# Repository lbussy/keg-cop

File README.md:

# Keg Cop

*Beverage Lines, Monitored.*

Keg Cop is an inexpensive and, most of all, simple to operate WiFi-enabled solution to maintain information about your Keezer, Kegerator, and Kegs.  Keg Cop enables you to use flowmeters of your choice (Swissflow during development) to monitor the contents of your kegs, and it even has a built-in Web UI to display what is on tap and how much is left.

Keg Cop uses an inexpensive ESP32 controller to control and monitor all aspects of your beverage dispensing solution.  If you already have flowmeters from another project, you can easily use those and upgrade your approach.  It will support one to nine flowmeters, and it will even control your temperatures for you.

You may employ up to five different temperature sensors to show you things like tower temp, keg temp, top and bottom of your Keezer, and you can even monitor the room temperature.

I designed this project as a complete system from the ground up.  Everything is provided, including board files for PCBs and 3D models for cases.  I’m releasing this system as something which provides either a complete recipe for success or enough information to allow you to roll your own if that’s your thing.

Whether you have one flowmeter or nine, Keg Cop can handle them.  Have more?  Add another controller, and KegScreen (coming soon!) will seamlessly display them all.

Want even more capabilities?  Keg Cop will report pours to Raspberry Pints via MQTT or a web endpoint with a generic JSON packet.
Still not enough?  Keg Cop was designed alongside KegScreen to work hand in hand with this exciting upcoming full-featured tap list solution.

Full documentation is provided, including the API and hardware assembly.  Or, if you are a more nuts and bolts person, GitHub may be the place for you!

Links and Support:

-	Home Page
-	Project on GitHub
-	Documentation
-	Report an Issue or Bug
-	Get support or chat with other users

This release has been a long time coming, and I’m excited to share this with you.  I want to thank the following folks from Homebrewtalk who have contributed in one way or another:

-	@thorrak
-	@gromitdj
-	@UncleD
-	@day_trippr
-	@cripplecreek

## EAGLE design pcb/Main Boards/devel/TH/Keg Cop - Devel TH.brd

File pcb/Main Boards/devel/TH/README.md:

# Development Board

It is exceedingly unlikely that anyone but me will need this PCB.

I designed this to allow me a physical interface into the software for development work.  This provides pushbuttons for emulating flowmeters, and a few DS18B20's for temperature values.

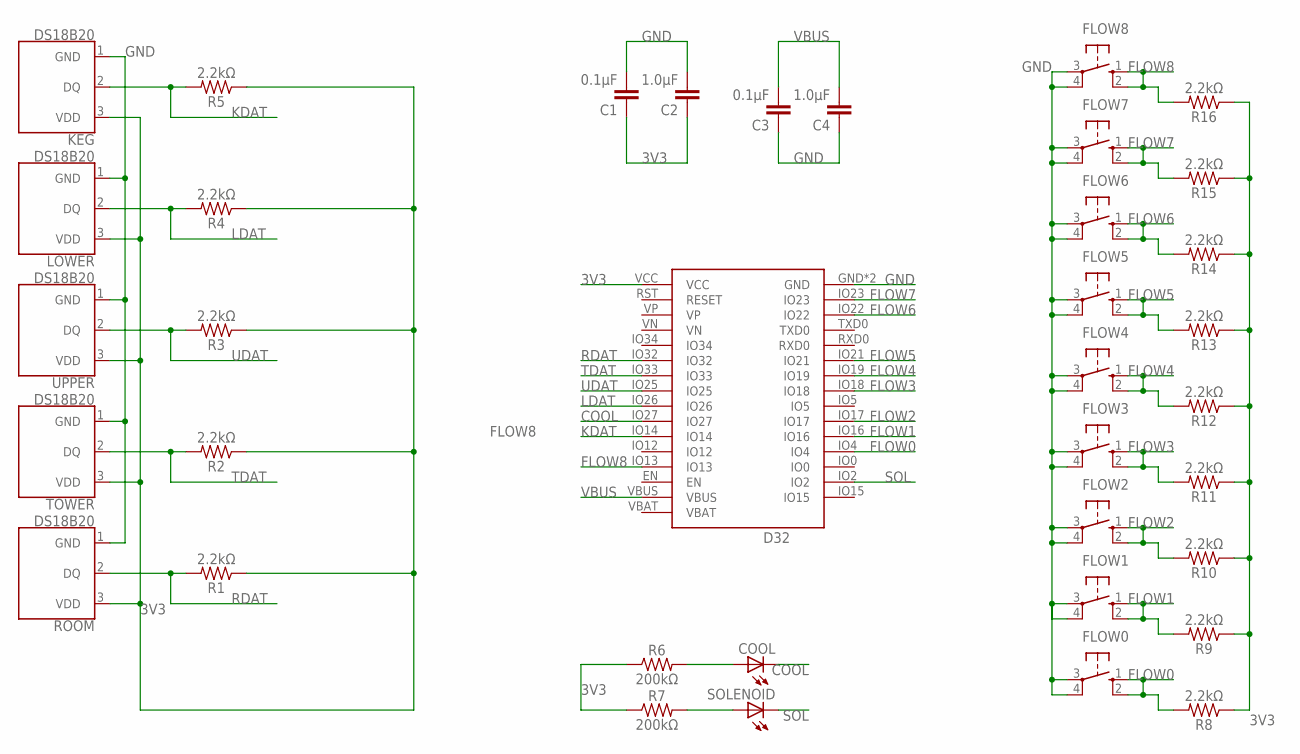
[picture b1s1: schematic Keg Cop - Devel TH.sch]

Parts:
C1, C3: 0.1μF; CAP_PTH-2.54
C2, C4: 1.0μF; CAP_PTH-2.54
COOL: LED3MM
D32: Lolin D32; D32_NO_BATT
FLOW0, FLOW1, FLOW2, FLOW3, FLOW4, FLOW5, FLOW6, FLOW7, FLOW8: 10-XX; B3F-10XX
KEG: DS18B20; TO-92-AMMO
LOWER: DS18B20; TO-92-AMMO
R1, R2, R3, R4, R5, R8, R9, R10, R11, R12, R13, R14, R15, R16: 2.2kΩ; AXIAL-0.3
R6, R7: 200kΩ; AXIAL-0.3
ROOM: DS18B20; TO-92-AMMO
SOLENOID: LED3MM
TOWER: DS18B20; TO-92-AMMO
UPPER: DS18B20; TO-92-AMMO

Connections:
3V3: C1.1, C2.1, D32.VCC, KEG.3 (VDD), LOWER.3 (VDD), R1.P$1 (1), R2.P$1 (1), R3.P$1 (1), R4.P$1 (1), R5.P$1 (1), R6.P$1 (1), R7.P$1 (1), R8.P$1 (1), R9.P$1 (1), R10.P$1 (1), R11.P$1 (1), R12.P$1 (1), R13.P$1 (1), R14.P$1 (1), R15.P$1 (1), R16.P$1 (1), ROOM.3 (VDD), TOWER.3 (VDD), UPPER.3 (VDD)
COOL: COOL.K (C), D32.IO27
FLOW0: D32.IO4, FLOW0.1 (S), FLOW0.2 (S1), R8.P$2 (2)
FLOW1: D32.IO16, FLOW1.1 (S), FLOW1.2 (S1), R9.P$2 (2)
FLOW2: D32.IO17, FLOW2.1 (S), FLOW2.2 (S1), R10.P$2 (2)
FLOW3: D32.IO18, FLOW3.1 (S), FLOW3.2 (S1), R11.P$2 (2)
FLOW4: D32.IO19, FLOW4.1 (S), FLOW4.2 (S1), R12.P$2 (2)
FLOW5: D32.IO21, FLOW5.1 (S), FLOW5.2 (S1), R13.P$2 (2)
FLOW6: D32.IO22, FLOW6.1 (S), FLOW6.2 (S1), R14.P$2 (2)
FLOW7: D32.IO23, FLOW7.1 (S), FLOW7.2 (S1), R15.P$2 (2)
FLOW8: D32.IO13, FLOW8.1 (S), FLOW8.2 (S1), R16.P$2 (2)
GND: C1.2, C2.2, C3.1, C4.1, D32.GND, D32.GND2 (GND), FLOW0.3, FLOW0.4 (P1), FLOW1.3, FLOW1.4 (P1), FLOW2.3, FLOW2.4 (P1), FLOW3.3, FLOW3.4 (P1), FLOW4.3, FLOW4.4 (P1), FLOW5.3, FLOW5.4 (P1), FLOW6.3, FLOW6.4 (P1), FLOW7.3, FLOW7.4 (P1), FLOW8.3, FLOW8.4 (P1), KEG.1 (GND), LOWER.1 (GND), ROOM.1 (GND), TOWER.1 (GND), UPPER.1 (GND)
KDAT: D32.IO14, KEG.2 (DQ), R5.P$2 (2)
LDAT: D32.IO26, LOWER.2 (DQ), R4.P$2 (2)
unnamed: COOL.A, R6.P$2 (2)
unnamed: R7.P$2 (2), SOLENOID.A
RDAT: D32.IO32, R1.P$2 (2), ROOM.2 (DQ)
SOL: D32.IO2, SOLENOID.K (C)
TDAT: D32.IO33, R2.P$2 (2), TOWER.2 (DQ)
UDAT: D32.IO25, R3.P$2 (2), UPPER.2 (DQ)
VBUS: C3.2, C4.2, D32.VBUS

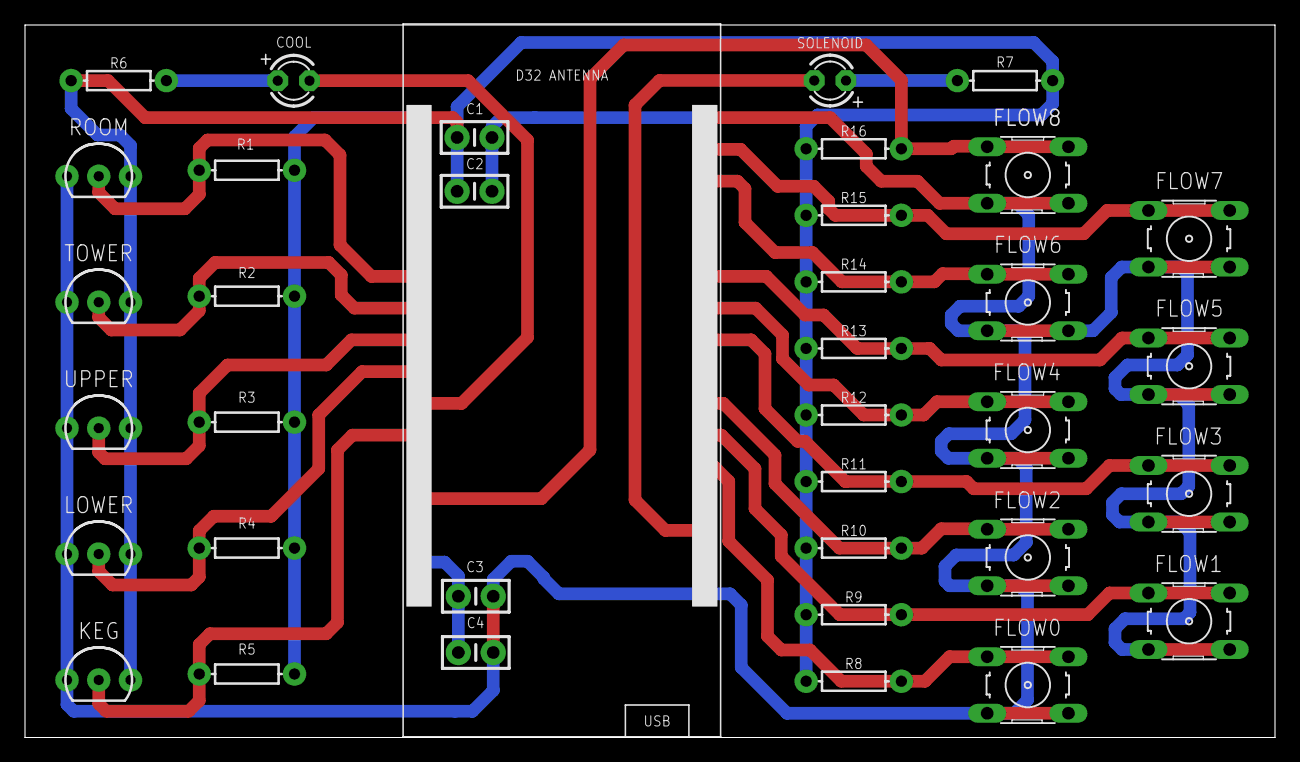
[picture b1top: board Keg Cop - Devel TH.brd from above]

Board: 2 copper layers, 100.0 x 57.0 mm, 37 parts (0 on the bottom side), 21 nets.

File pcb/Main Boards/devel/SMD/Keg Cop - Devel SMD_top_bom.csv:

Comment,Designator,Footprint,LCSC Part #
0.1µF,C1 C3,SMD-0805,C28233
1.0µF,C2 C4,SMD-0805,C28323
2k2½,R1 R2 R3 R4 R5 R6 R7 R8 R9 R12 R13 R14 R15 R16,SMD-0805,C17518
60.4½,R10 R11,SMD-0805,C25323
DS18B20Z,KEG LOWER ROOM TOWER UPPER,SOIC127P600X175-8N,C695837
LED_0603LED_SMD_0603,COOL SOLENOID,LED_SMD_0603,C2286
TS08-66-43-BK-160-SMT-67,FLOW0 FLOW1 FLOW2 FLOW3 FLOW4 FLOW5 FLOW6 FLOW7 FLOW8,SW_TS08-66-43-BK-160-SMT-67,C2889023

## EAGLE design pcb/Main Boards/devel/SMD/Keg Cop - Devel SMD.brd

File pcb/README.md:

# Printed Circuit Boards for Keg Cop

Contained here are two folders:

- **Main Boards:** Boards which receive the D32 controller, and provide connectivity to the breakouts.
- **Breakouts:** Boards which distribute and receive signals within the kegerator/keezer.

The type and number required of each board will vary by the intended configuration.  Use [the documentation](https://docs.kegcop.com) to determine which boards you need and how many:

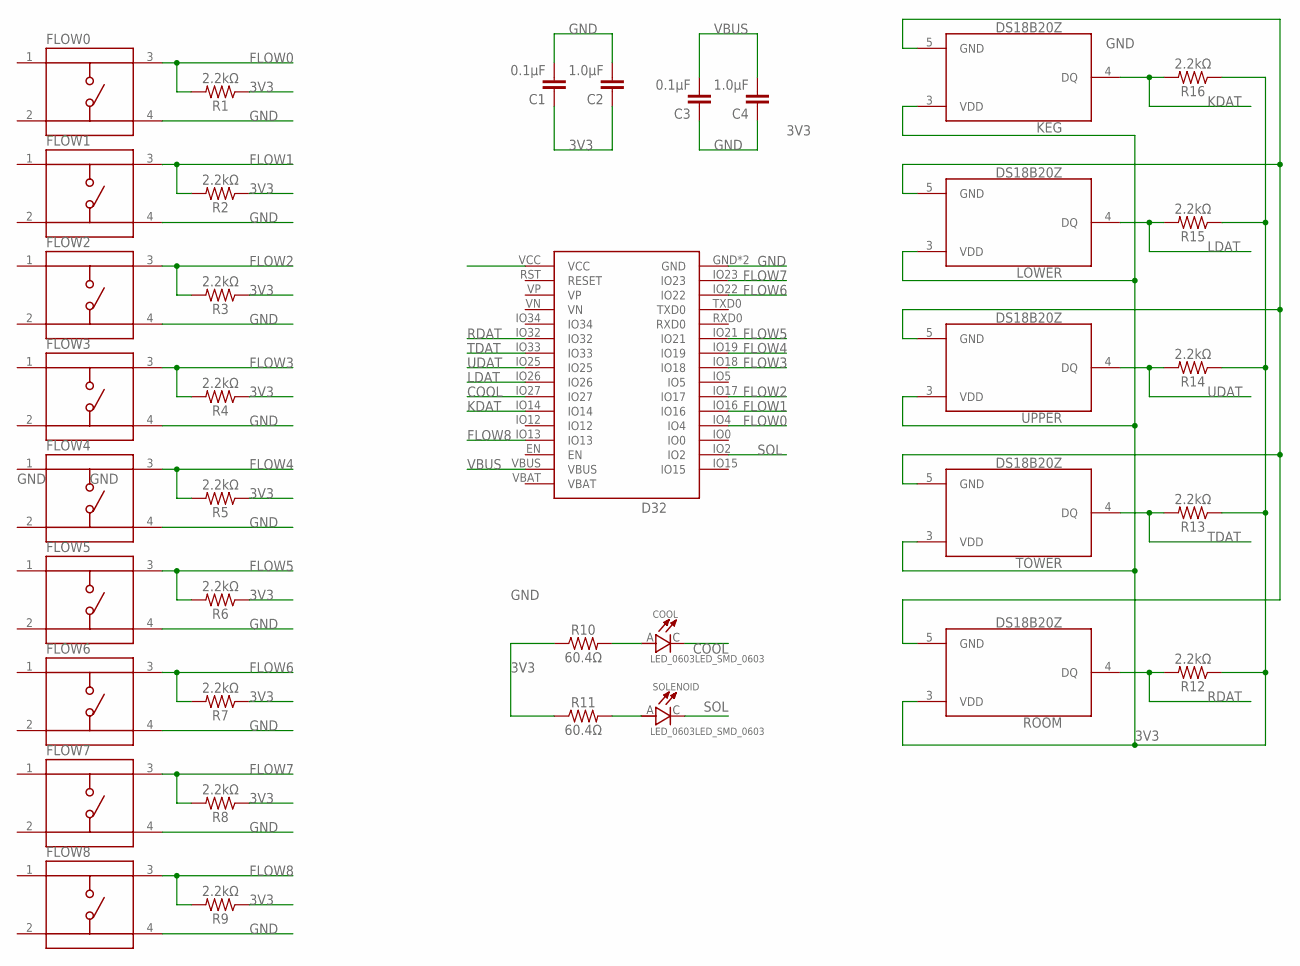
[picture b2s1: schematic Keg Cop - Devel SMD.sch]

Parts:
C1, C3: 0.1μF; SMD-0805
C2, C4: 1.0μF; SMD-0805
COOL: LED_0603LED_SMD_0603; LED_SMD_0603
D32: Lolin D32; D32_NO_BATT
FLOW0, FLOW1, FLOW2, FLOW3, FLOW4, FLOW5, FLOW6, FLOW7, FLOW8: TS08-66-43-BK-160-SMT-67; SW_TS08-66-43-BK-160-SMT-67
KEG: DS18B20Z; SOIC127P600X175-8N
LOWER: DS18B20Z; SOIC127P600X175-8N
R1, R2, R3, R4, R5, R6, R7, R8, R9, R12, R13, R14, R15, R16: 2.2kΩ; SMD-0805
R10, R11: 60.4Ω; SMD-0805
ROOM: DS18B20Z; SOIC127P600X175-8N
SOLENOID: LED_0603LED_SMD_0603; LED_SMD_0603
TOWER: DS18B20Z; SOIC127P600X175-8N
UPPER: DS18B20Z; SOIC127P600X175-8N

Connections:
3V3: C1.1, C2.1, D32.VCC, KEG.3 (VDD), LOWER.3 (VDD), R1.1, R2.1, R3.1, R4.1, R5.1, R6.1, R7.1, R8.1, R9.1, R10.1, R11.1, R12.1, R13.1, R14.1, R15.1, R16.1, ROOM.3 (VDD), TOWER.3 (VDD), UPPER.3 (VDD)
COOL: COOL.C, D32.IO27
FLOW0: D32.IO4, FLOW0.3, R1.2
FLOW1: D32.IO16, FLOW1.3, R2.2
FLOW2: D32.IO17, FLOW2.3, R3.2
FLOW3: D32.IO18, FLOW3.3, R4.2
FLOW4: D32.IO19, FLOW4.3, R5.2
FLOW5: D32.IO21, FLOW5.3, R6.2
FLOW6: D32.IO22, FLOW6.3, R7.2
FLOW7: D32.IO23, FLOW7.3, R8.2
FLOW8: D32.IO13, FLOW8.3, R9.2
GND: C1.2, C2.2, C3.1, C4.1, D32.GND, D32.GND2 (GND), FLOW0.4, FLOW1.4, FLOW2.4, FLOW3.4, FLOW4.4, FLOW5.4, FLOW6.4, FLOW7.4, FLOW8.4, KEG.5 (GND), LOWER.5 (GND), ROOM.5 (GND), TOWER.5 (GND), UPPER.5 (GND)
KDAT: D32.IO14, KEG.4 (DQ), R16.2
LDAT: D32.IO26, LOWER.4 (DQ), R15.2
unnamed: COOL.A, R10.2
unnamed: R11.2, SOLENOID.A
RDAT: D32.IO32, R12.2, ROOM.4 (DQ)
SOL: D32.IO2, SOLENOID.C
TDAT: D32.IO33, R13.2, TOWER.4 (DQ)
UDAT: D32.IO25, R14.2, UPPER.4 (DQ)
VBUS: C3.2, C4.2, D32.VBUS

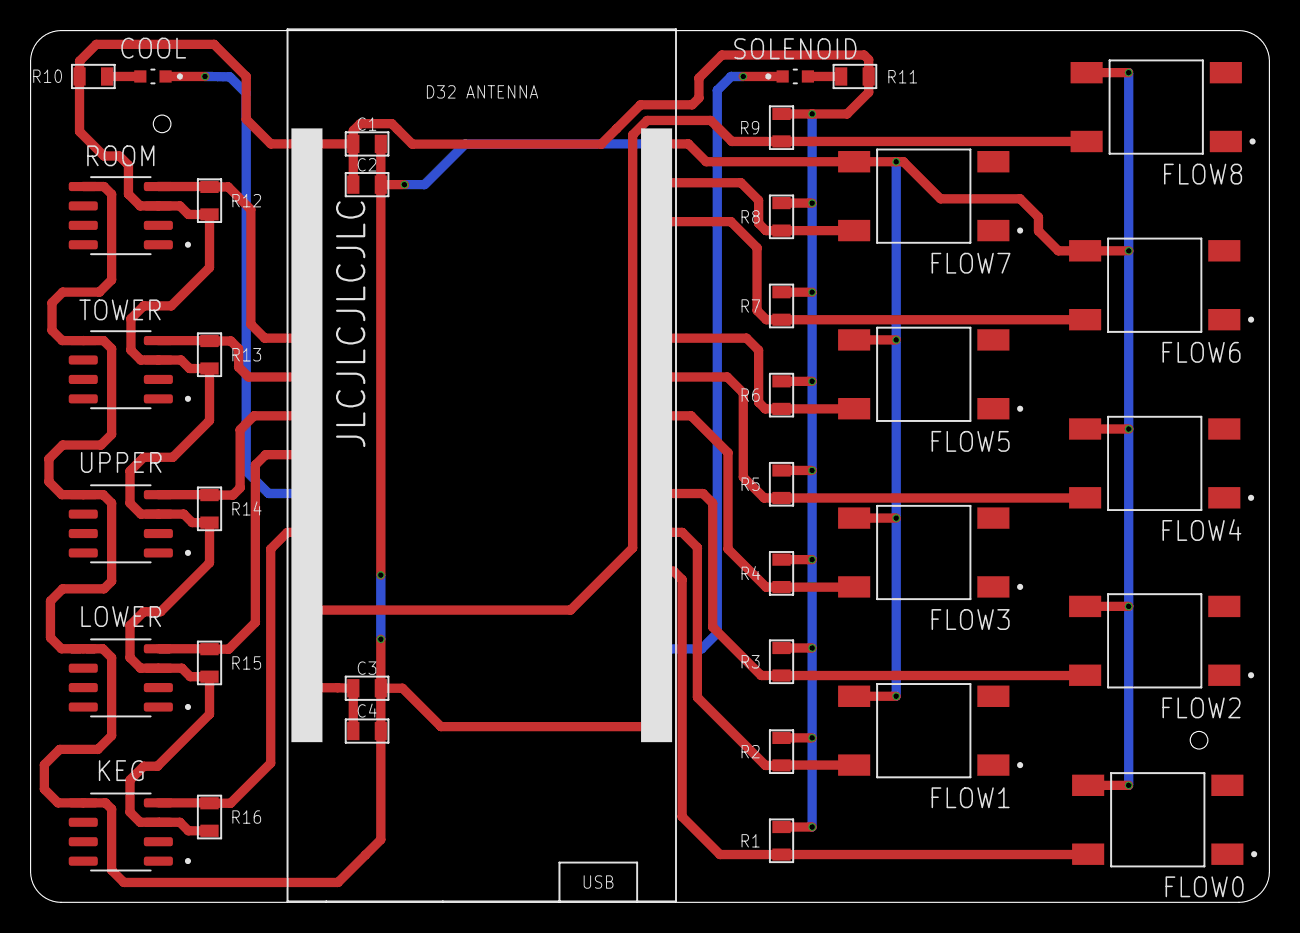
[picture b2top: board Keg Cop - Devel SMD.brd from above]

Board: 2 copper layers, 81.0 x 57.0 mm, 39 parts (0 on the bottom side), 21 nets.

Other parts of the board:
U$1, U$2: 1.152

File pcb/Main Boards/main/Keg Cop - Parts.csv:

"Part";"Value";"Device";"Package";"Description";"ARROW_PART_NUMBER";"ARROW_PRICE-STOCK";"DESCRIPTION";"HEIGHT";"MANUFACTURER_NAME";"MANUFACTURER_PART_NUMBER";"MF";"MOUSER_PART_NUMBER";"MOUSER_PRICE-STOCK";"MPN";"OC_FARNELL";"OC_NEWARK";"POPULARITY";"PROD_ID";"VALUE";
"C1";"0.1μF";"CAP_CERAMIC_2.54";"CAP_PTH-2.54";"";"";"";"";"";"";"";"";"";"";"";"";"";"";"";"";
"C2";"1.0μF";"CAP_CERAMIC_2.54";"CAP_PTH-2.54";"";"";"";"";"";"";"";"";"";"";"";"";"";"";"";"";
"C3";"0.1μF";"CAP_CERAMIC_2.54";"CAP_PTH-2.54";"";"";"";"";"";"";"";"";"";"";"";"";"";"";"";"";
"C4";"1.0μF";"CAP_CERAMIC_2.54";"CAP_PTH-2.54";"";"";"";"";"";"";"";"";"";"";"";"";"";"";"";"";
"D32";"Lolin D32";"WEMOS-D32D32_NO_BATT";"D32_NO_BATT";"D32_REVERSE is a Reverse silkscreen for placing the Wemos D32 on the underside of the board";"";"";"";"";"";"";"";"";"";"";"";"";"";"";"";
"IC1";"DS18B20+";"DS18B20+";"TO-92";"DS18B20 prog thermometer 1-Wire, TO92";"DS18B20+";"";"DS18B20 prog thermometer 1-Wire, TO92";"mm";"Maxim Integrated";"DS18B20+";"";"700-DS18B20+";"https://www.mouser.co.uk/ProductDetail/Maxim-Integrated/DS18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";"";"";"";"";"";"";
"POWER";"2-PIN";"HDR-2";"HDR-2_VERT";"";"";"";"";"";"";"";"";"";"";"";"";"";"";"";"";
"R1";"2.2kΩ";"RESISTORAXIAL-0.3";"AXIAL-0.3";"Generic Resistor Package";"";"";"";"";"";"";"";"";"";"";"";"";"";" ";" ";
"R2";"2.2kΩ";"RESISTORAXIAL-0.3";"AXIAL-0.3";"Generic Resistor Package";"";"";"";"";"";"";"";"";"";"";"";"";"";" ";" ";
"R3";"2.2kΩ";"RESISTORAXIAL-0.3";"AXIAL-0.3";"Generic Resistor Package";"";"";"";"";"";"";"";"";"";"";"";"";"";" ";" ";
"R4";"2.2kΩ";"RESISTORAXIAL-0.3";"AXIAL-0.3";"Generic Resistor Package";"";"";"";"";"";"";"";"";"";"";"";"";"";" ";" ";
"R5";"2.2kΩ";"RESISTORAXIAL-0.3";"AXIAL-0.3";"Generic Resistor Package";"";"";"";"";"";"";"";"";"";"";"";"";"";" ";" ";
"R6";"2.2kΩ";"RESISTORAXIAL-0.3";"AXIAL-0.3";"Generic Resistor Package";"";"";"";"";"";"";"";"";"";"";"";"";"";" ";" ";
"R7";"2.2kΩ";"RESISTORAXIAL-0.3";"AXIAL-0.3";"Generic Resistor Package";"";"";"";"";"";"";"";"";"";"";"";"";"";" ";" ";
"R8";"2.2kΩ";"RESISTORAXIAL-0.3";"AXIAL-0.3";"Generic Resistor Package";"";"";"";"";"";"";"";"";"";"";"";"";"";" ";" ";
"R9";"2.2kΩ";"RESISTORAXIAL-0.3";"AXIAL-0.3";"Generic Resistor Package";"";"";"";"";"";"";"";"";"";"";"";"";"";" ";" ";
"R10";"2.2kΩ";"RESISTORAXIAL-0.3";"AXIAL-0.3";"Generic Resistor Package";"";"";"";"";"";"";"";"";"";"";"";"";"";" ";" ";
"R11";"2.2kΩ";"RESISTORAXIAL-0.3";"AXIAL-0.3";"Generic Resistor Package";"";"";"";"";"";"";"";"";"";"";"";"";"";" ";" ";
"R12";"2.2kΩ";"RESISTORAXIAL-0.3";"AXIAL-0.3";"Generic Resistor Package";"";"";"";"";"";"";"";"";"";"";"";"";"";" ";" ";
"R13";"2.2kΩ";"RESISTORAXIAL-0.3";"AXIAL-0.3";"Generic Resistor Package";"";"";"";"";"";"";"";"";"";"";"";"";"";" ";" ";
"R14";"2.2kΩ";"RESISTORAXIAL-0.3";"AXIAL-0.3";"Generic Resistor Package";"";"";"";"";"";"";"";"";"";"";"";"";"";" ";" ";
"RELAY";"4-PIN";"MA04-1";"MA04-1";"PIN HEADER";"";"";"";"";"";"";"";"";"";"";"unknown";"unknown";"41";"";"";
"ROOM";"3-PIN";"HDR-3";"HDR-3_VERT";"PIN HEADER";"";"";"";"";"";"";"";"";"";"";"";"";"";"";"";
"X1";"RJ45-8X";"RJ45-8X";"RJ45-NO-SHIELD";"CORCOM Modular RJ Jacks No Shield";"";"";"";"";"";"";"";"";"";"RJ45-8X";"unknown";"16R6101";"0";"";"";
"X2";"RJ45-8X";"RJ45-8X";"RJ45-NO-SHIELD";"CORCOM Modular RJ Jacks No Shield";"";"";"";"";"";"";"";"";"";"RJ45-8X";"unknown";"16R6101";"0";"";"";
"X3";"RJ45-8X";"RJ45-8X";"RJ45-NO-SHIELD";"CORCOM Modular RJ Jacks No Shield";"";"";"";"";"";"";"";"";"";"RJ45-8X";"unknown";"16R6101";"0";"";"";
"X4";"RJ45-8X";"RJ45-8X";"RJ45-NO-SHIELD";"CORCOM Modular RJ Jacks No Shield";"";"";"";"";"";"";"";"";"";"RJ45-8X";"unknown";"16R6101";"0";"";"";

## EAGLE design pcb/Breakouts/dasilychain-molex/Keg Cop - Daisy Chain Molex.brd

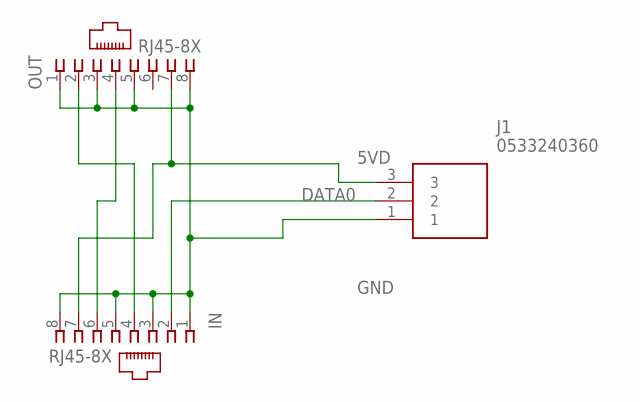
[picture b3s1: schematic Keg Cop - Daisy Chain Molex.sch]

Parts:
IN: RJ45-8X; RJ45-NO-SHIELD
J1: 0533240360
OUT: RJ45-8X; RJ45-NO-SHIELD

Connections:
5VD: IN.7, J1.3, OUT.7
DATA0: IN.2, J1.2
DATA1: IN.4, OUT.2
DATA2: IN.6, OUT.4
GND: IN.1, IN.3, IN.5, IN.8, J1.1, OUT.1, OUT.3, OUT.5, OUT.8

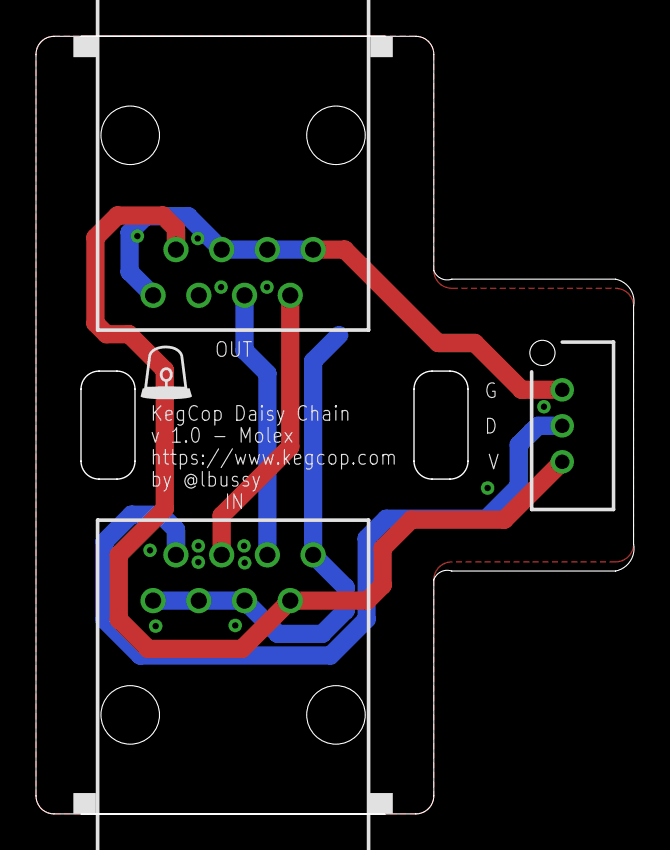
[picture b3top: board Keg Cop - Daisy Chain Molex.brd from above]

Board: 2 copper layers, 33.2 x 43.2 mm, 3 parts (0 on the bottom side), 5 nets.

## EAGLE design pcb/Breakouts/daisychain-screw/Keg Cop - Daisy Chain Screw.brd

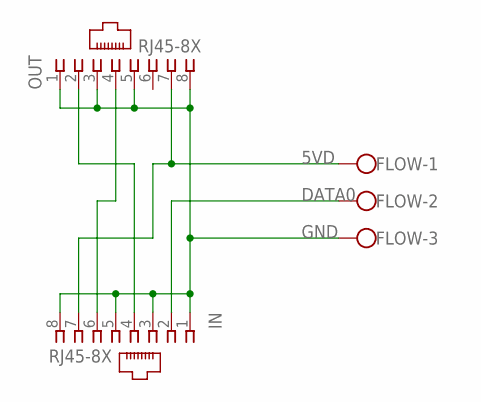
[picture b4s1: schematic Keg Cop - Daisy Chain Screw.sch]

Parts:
FLOW: W237-103
IN: RJ45-8X; RJ45-NO-SHIELD
OUT: RJ45-8X; RJ45-NO-SHIELD

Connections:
5VD: FLOW.1, IN.7, OUT.7
DATA0: FLOW.2, IN.2
DATA1: IN.4, OUT.2
DATA2: IN.6, OUT.4
GND: FLOW.3, IN.1, IN.3, IN.5, IN.8, OUT.1, OUT.3, OUT.5, OUT.8

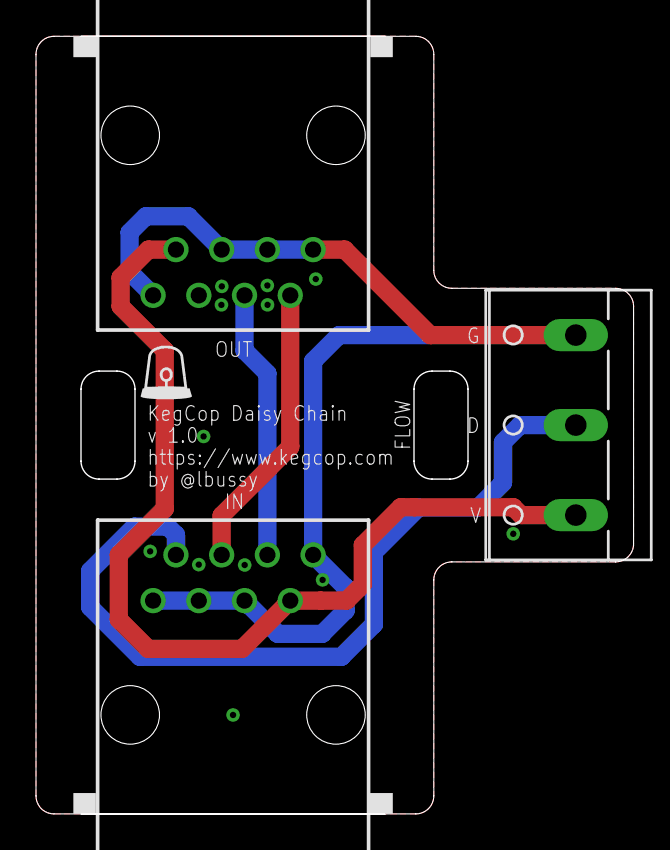
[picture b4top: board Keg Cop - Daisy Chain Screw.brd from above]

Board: 2 copper layers, 33.2 x 43.2 mm, 3 parts (0 on the bottom side), 5 nets.

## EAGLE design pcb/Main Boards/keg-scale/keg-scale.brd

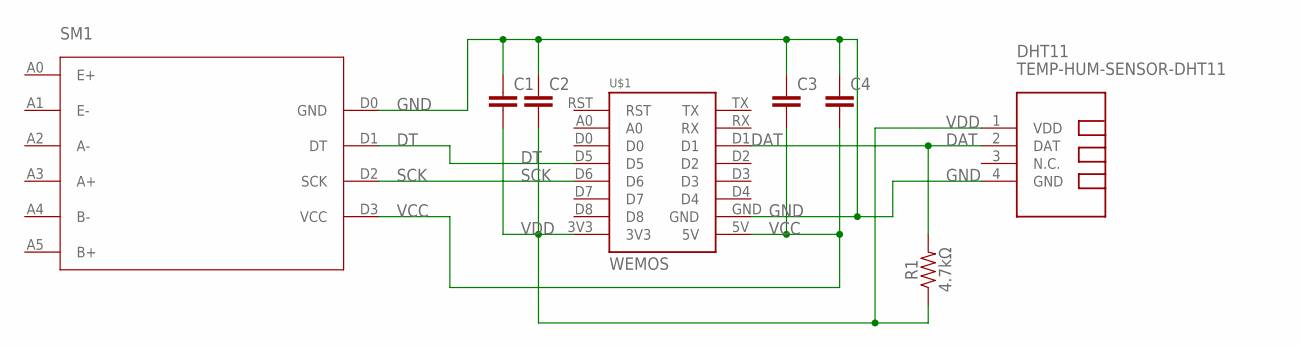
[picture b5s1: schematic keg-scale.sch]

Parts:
C1, C2, C3, C4: C5/3; C5B3
DHT11: TEMP-HUM-SENSOR-DHT11
R1: 4.7kΩ; AXIAL-0.3
SM1: HX711
U$1: WEMOS

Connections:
DAT: DHT11.2 (DAT), R1.P$2 (2), U$1.D1
DT: SM1.D1 (DT), U$1.D5
GND: C1.1, C2.1, C3.1, C4.1, DHT11.4 (GND), SM1.D0 (GND), U$1.GND
SCK: SM1.D2 (SCK), U$1.D6
VCC: C3.2, C4.2, SM1.D3 (VCC), U$1.5V
VDD: C1.2, C2.2, DHT11.1 (VDD), R1.P$1 (1), U$1.3V3

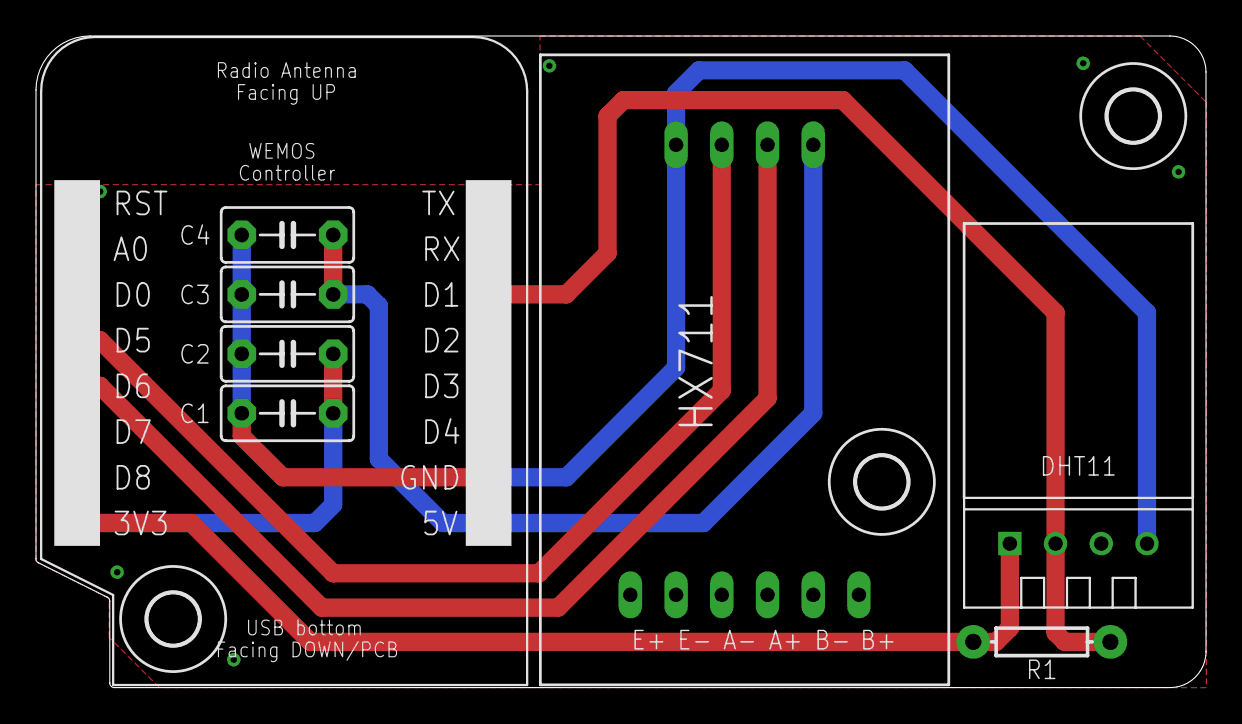
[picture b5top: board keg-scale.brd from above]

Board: 2 copper layers, 65.0 x 36.2 mm, 11 parts (0 on the bottom side), 6 nets.

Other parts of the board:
U$2, U$3, U$4: 2,8

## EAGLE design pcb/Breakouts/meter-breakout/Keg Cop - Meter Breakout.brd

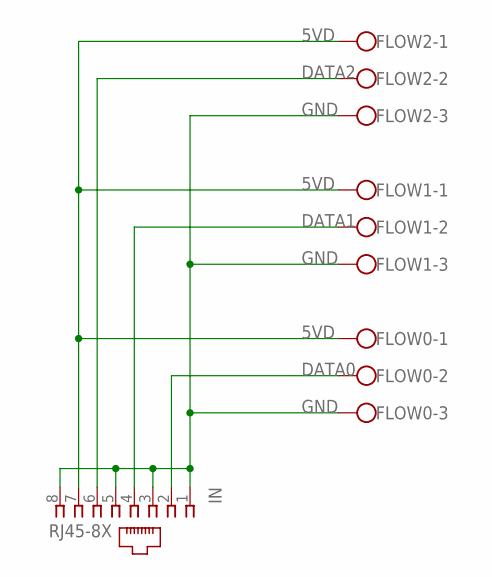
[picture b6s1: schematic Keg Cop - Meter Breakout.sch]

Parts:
FLOW0, FLOW1, FLOW2: W237-103
IN: RJ45-8X; RJ45-NO-SHIELD

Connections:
5VD: FLOW0.1, FLOW1.1, FLOW2.1, IN.7
DATA0: FLOW0.2, IN.2
DATA1: FLOW1.2, IN.4
DATA2: FLOW2.2, IN.6
GND: FLOW0.3, FLOW1.3, FLOW2.3, IN.1, IN.3, IN.5, IN.8

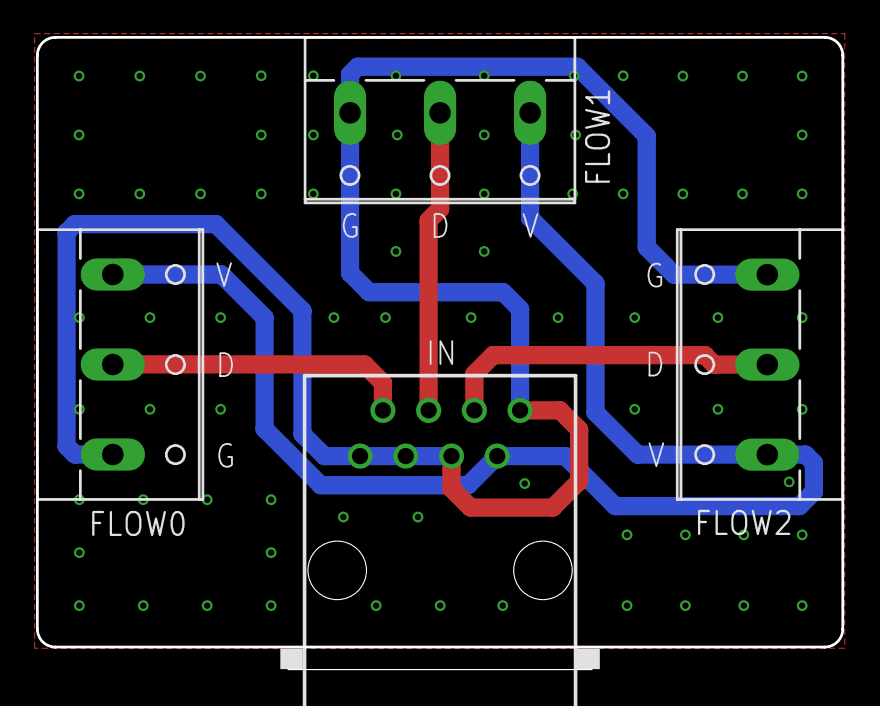
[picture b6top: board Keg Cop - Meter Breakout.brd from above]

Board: 2 copper layers, 44.7 x 35.1 mm, 4 parts (0 on the bottom side), 5 nets.

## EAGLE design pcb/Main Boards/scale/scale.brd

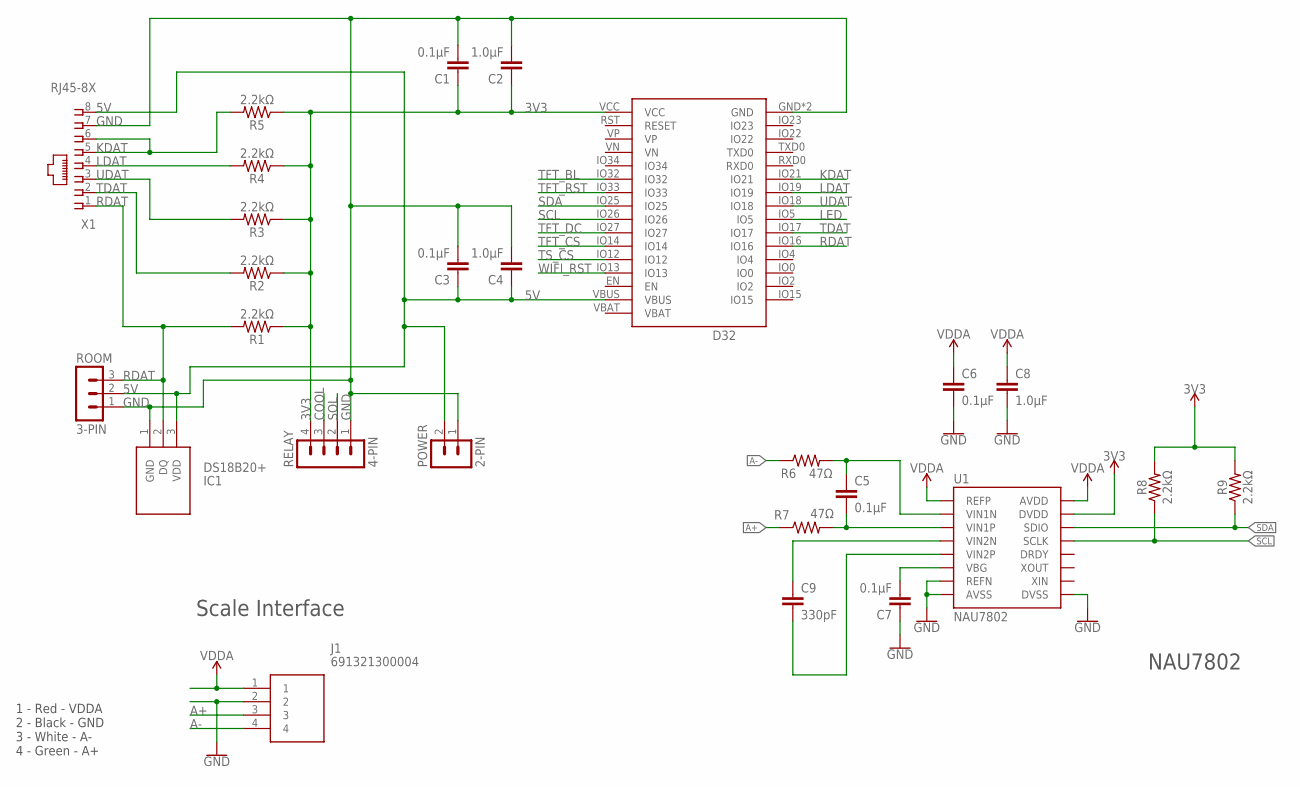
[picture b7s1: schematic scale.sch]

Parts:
C1, C3, C5, C6, C7: 0.1μF; CAP_PTH-2.54
C2, C4, C8: 1.0μF; CAP_PTH-2.54
C9: 330pF; CAP_PTH-2.54
D32: Lolin D32; D32_NO_BATT
IC1: DS18B20+; TO-92
J1: 691321300004; SHDR4W80P0X381_1X4_1643X720X92
POWER: 2-PIN; HDR-2_VERT
R1, R2, R3, R4, R5, R8, R9: 2.2kΩ; AXIAL-0.3
R6, R7: 47Ω; AXIAL-0.3
RELAY: 4-PIN; MA04-1
ROOM: 3-PIN; HDR-3_VERT
U1: NAU7802; DIP16
X1: RJ45-8X; RJ45-NO-SHIELD

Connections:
3V3: C1.1, C2.1, D32.VCC, R1.P$1 (1), R2.P$1 (1), R3.P$1 (1), R4.P$1 (1), R5.P$1 (1), R8.P$2 (2), R9.P$2 (2), RELAY.4, U1.15 (DVDD)
5V: C3.1, C4.1, D32.VBUS, IC1.3 (VDD), POWER.2, ROOM.2, X1.8
A+: J1.3, R7.P$1 (1)
A-: J1.4, R6.P$1 (1)
B+: C9.2, U1.5 (VIN2P)
COOL: RELAY.3
GND: C1.2, C2.2, C3.2, C4.2, C6.2, C7.1, C8.2, D32.GND, D32.GND2 (GND), IC1.1 (GND), J1.2, POWER.1, RELAY.1, ROOM.1, U1.7 (REFN), U1.8 (AVSS), U1.9 (DVSS), X1.7
KDAT: D32.IO21, R5.P$2 (2), X1.5, X1.6
LDAT: D32.IO19, R4.P$2 (2), X1.4
LED: D32.IO5
unnamed: C9.1, U1.4 (VIN2N)
unnamed: C7.2, U1.6 (VBG)
unnamed: C5.2, R7.P$2 (2), U1.3 (VIN1P)
unnamed: C5.1, R6.P$2 (2), U1.2 (VIN1N)
RDAT: D32.IO16, IC1.2 (DQ), R1.P$2 (2), ROOM.3, X1.1
SCL: D32.IO26, R8.P$1 (1), U1.13 (SCLK)
SDA: D32.IO25, R9.P$1 (1), U1.14 (SDIO)
SOL: RELAY.2
TDAT: D32.IO17, R2.P$2 (2), X1.2
TFT_BL: D32.IO32
TFT_CS: D32.IO14
TFT_DC: D32.IO27
TFT_RST: D32.IO33
TS_CS: D32.IO12
UDAT: D32.IO18, R3.P$2 (2), X1.3
VDDA: C6.1, C8.1, J1.1, U1.1 (REFP), U1.16 (AVDD)
WIFI_RST: D32.IO13

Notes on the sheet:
NAU7802
Scale Interface
1 - Red - VDDA 2 - Black - GND 3 - White - A- 4 - Green - A+

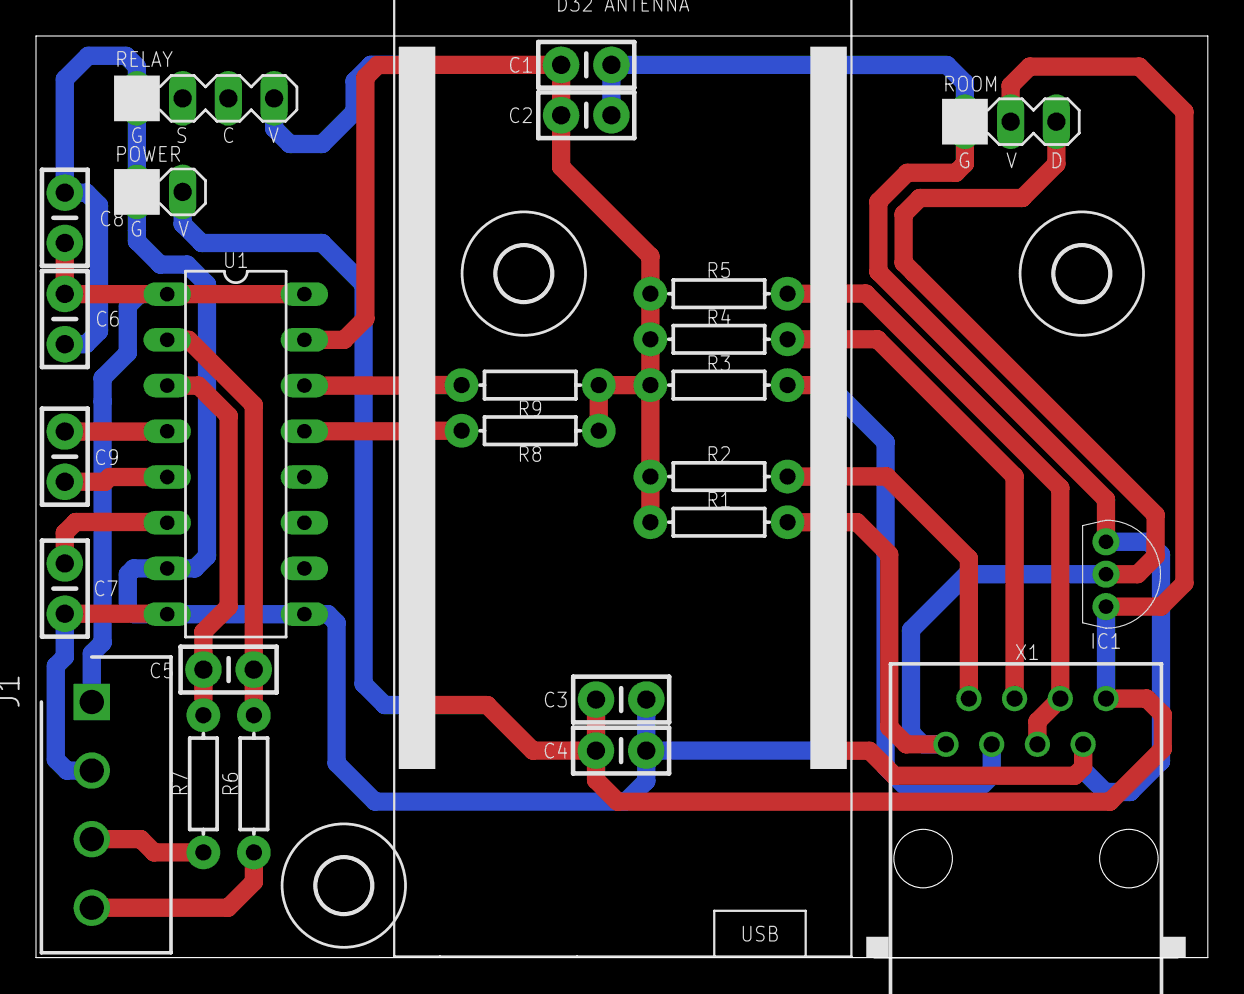
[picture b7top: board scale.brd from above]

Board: 2 copper layers, 65.1 x 51.2 mm, 29 parts (0 on the bottom side), 18 nets.

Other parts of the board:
U$1, U$2, U$3: 3,0

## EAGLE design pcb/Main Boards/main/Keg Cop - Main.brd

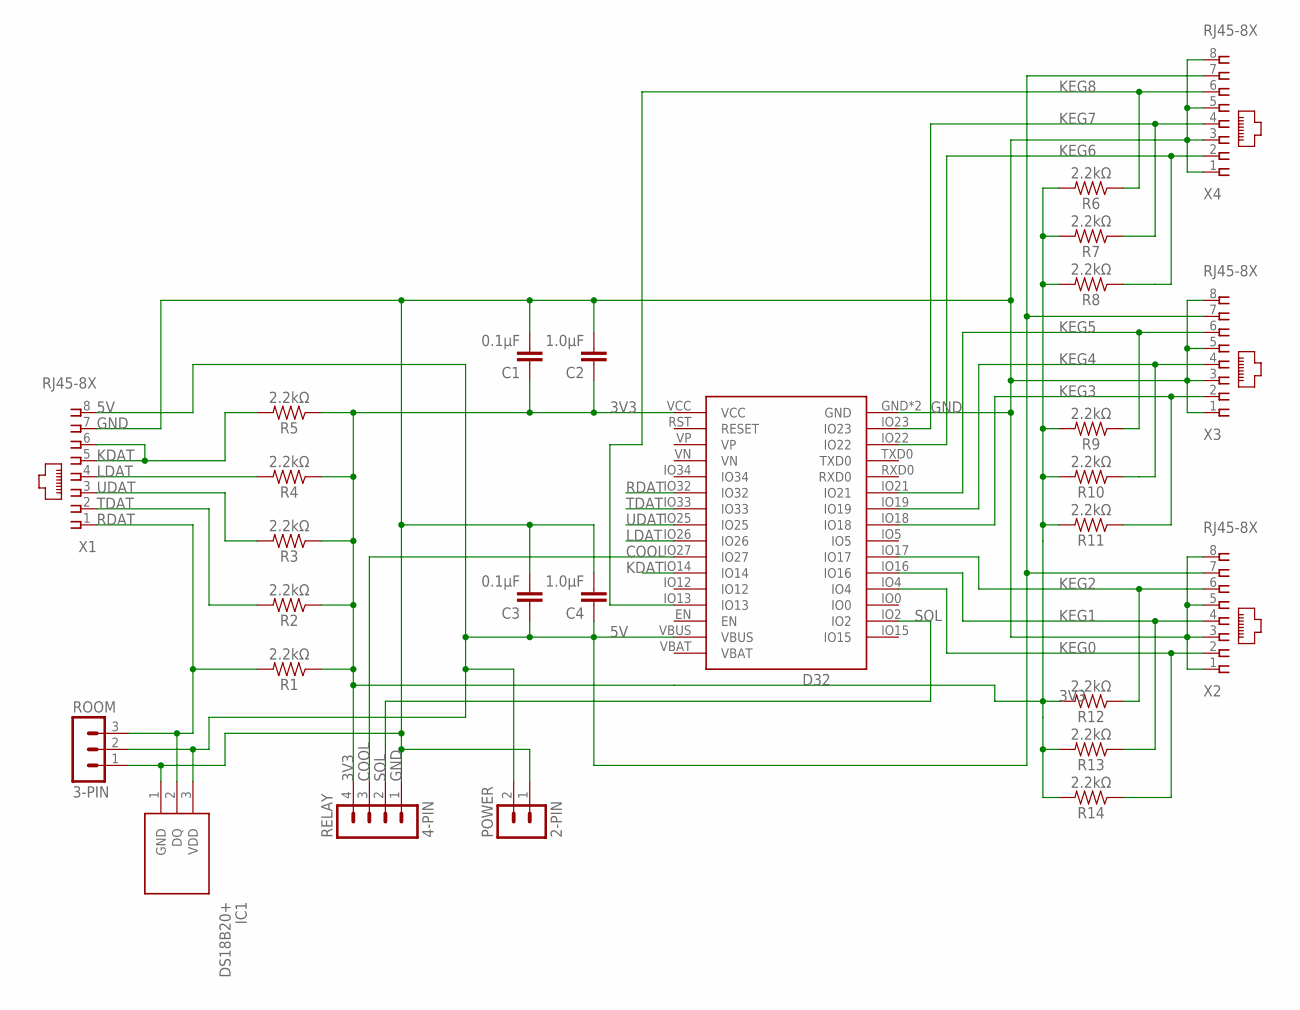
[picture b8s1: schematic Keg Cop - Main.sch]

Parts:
C1, C3: 0.1μF; CAP_PTH-2.54
C2, C4: 1.0μF; CAP_PTH-2.54
D32: Lolin D32; D32_NO_BATT
IC1: DS18B20+; TO-92
POWER: 2-PIN; HDR-2_VERT
R1, R2, R3, R4, R5, R6, R7, R8, R9, R10, R11, R12, R13, R14: 2.2kΩ; AXIAL-0.3
RELAY: 4-PIN; MA04-1
ROOM: 3-PIN; HDR-3_VERT
X1, X2, X3, X4: RJ45-8X; RJ45-NO-SHIELD

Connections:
3V3: C1.1, C2.1, D32.VCC, R1.P$1 (1), R2.P$1 (1), R3.P$1 (1), R4.P$1 (1), R5.P$1 (1), R6.P$2 (2), R7.P$2 (2), R8.P$2 (2), R9.P$2 (2), R10.P$2 (2), R11.P$2 (2), R12.P$2 (2), R13.P$2 (2), R14.P$2 (2), RELAY.4
5V: C3.1, C4.1, D32.VBUS, IC1.3 (VDD), POWER.2, ROOM.2, X1.8, X2.7, X3.7, X4.7
COOL: D32.IO27, RELAY.3
GND: C1.2, C2.2, C3.2, C4.2, D32.GND, D32.GND2 (GND), IC1.1 (GND), POWER.1, RELAY.1, ROOM.1, X1.7, X2.1, X2.3, X2.5, X2.8, X3.1, X3.3, X3.5, X3.8, X4.1, X4.3, X4.5, X4.8
KDAT: D32.IO14, R5.P$2 (2), X1.5, X1.6
KEG0: D32.IO4, R14.P$1 (1), X2.2
KEG1: D32.IO16, R13.P$1 (1), X2.4
KEG2: D32.IO17, R12.P$1 (1), X2.6
KEG3: D32.IO18, R11.P$1 (1), X3.2
KEG4: D32.IO19, R10.P$1 (1), X3.4
KEG5: D32.IO21, R9.P$1 (1), X3.6
KEG6: D32.IO22, R8.P$1 (1), X4.2
KEG7: D32.IO23, R7.P$1 (1), X4.4
KEG8: D32.IO13, R6.P$1 (1), X4.6
LDAT: D32.IO26, R4.P$2 (2), X1.4
RDAT: D32.IO32, IC1.2 (DQ), R1.P$2 (2), ROOM.3, X1.1
SOL: D32.IO2, RELAY.2
TDAT: D32.IO33, R2.P$2 (2), X1.2
UDAT: D32.IO25, R3.P$2 (2), X1.3

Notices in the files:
hold/flowmeter.cpp:
Copyright (C) 2019-2020 Lee C. Bussy (@LBussy)
src/config.h:
Copyright (C) 2019-2023 Lee C. Bussy (@LBussy)
parts and their libraries:
SparkFun-Resistors: Licensing: Creative Commons ShareAlike 4.0 International - https://creativecommons.org/licenses/by-sa/4.0
diy-modules: Released under the Creative Commons Attribution 4.0 International License: http://creativecommons.org/licenses/by/4.0
